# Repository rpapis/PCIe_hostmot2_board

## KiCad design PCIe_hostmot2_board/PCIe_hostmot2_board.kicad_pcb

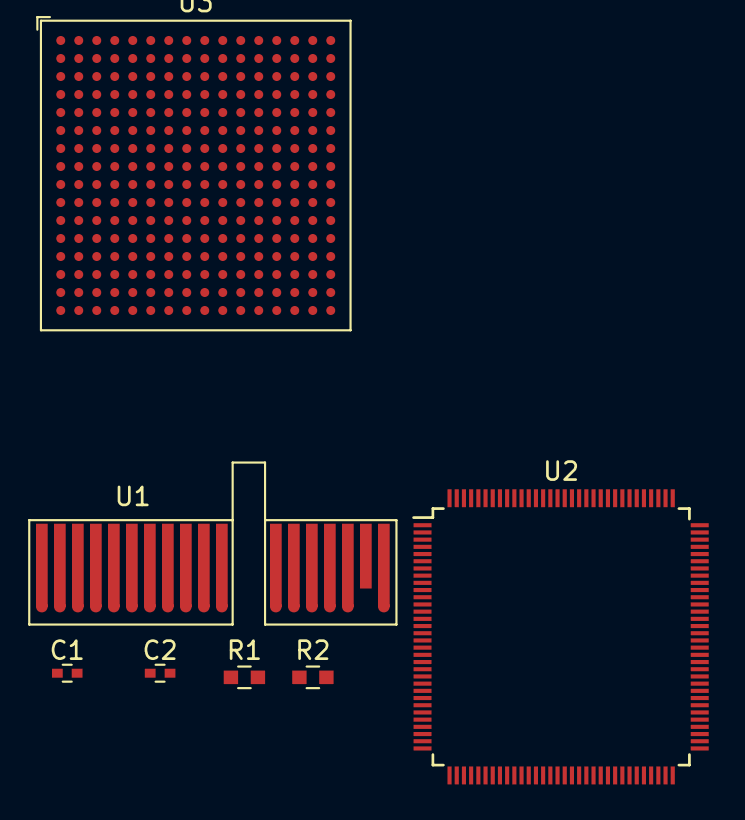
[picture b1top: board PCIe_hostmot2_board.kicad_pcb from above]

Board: 2 copper layers, 7 parts (0 on the bottom side), 14 nets, no tracks yet.

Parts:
C1, C2: 100nF; C_0402
R1: 14k3; C_0603
R2: 232; C_0603
U1: PCIe_x1; BUS_PCIexpress
U2: XIO2001_PNP_128; TQFP-128_14x14mm_Pitch0.4mm
U3: XC6SLX25-FTG256; BGA-256_16x16_17.0x17.0mm_Pitch1.0mm

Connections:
/PCIe/CLK_N: U1.A14, U2.94
/PCIe/CLK_P: U1.A13, U2.93
/PCIe/CTX_N: C2.2, U1.A17
/PCIe/CTX_P: C1.2, U1.A16
/PCIe/PERST: U1.A11, U2.77
/PCIe/RX_N: U1.B15, U2.88
/PCIe/RX_P: U1.B14, U2.87
/PCIe/TX_N: C2.1, U2.81
/PCIe/TX_P: C1.1, U2.80
/PCIe/WAKE: U1.B11, U2.68
GND: U1.A4, U1.A12, U1.A15, U1.A18, U1.B4, U1.B7, U1.B13, U1.B16, U1.B18
unnamed: R1.1, U2.71
unnamed: R1.2, R2.2
unnamed: R2.1, U2.72

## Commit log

2019-08-14 added XIO2001
